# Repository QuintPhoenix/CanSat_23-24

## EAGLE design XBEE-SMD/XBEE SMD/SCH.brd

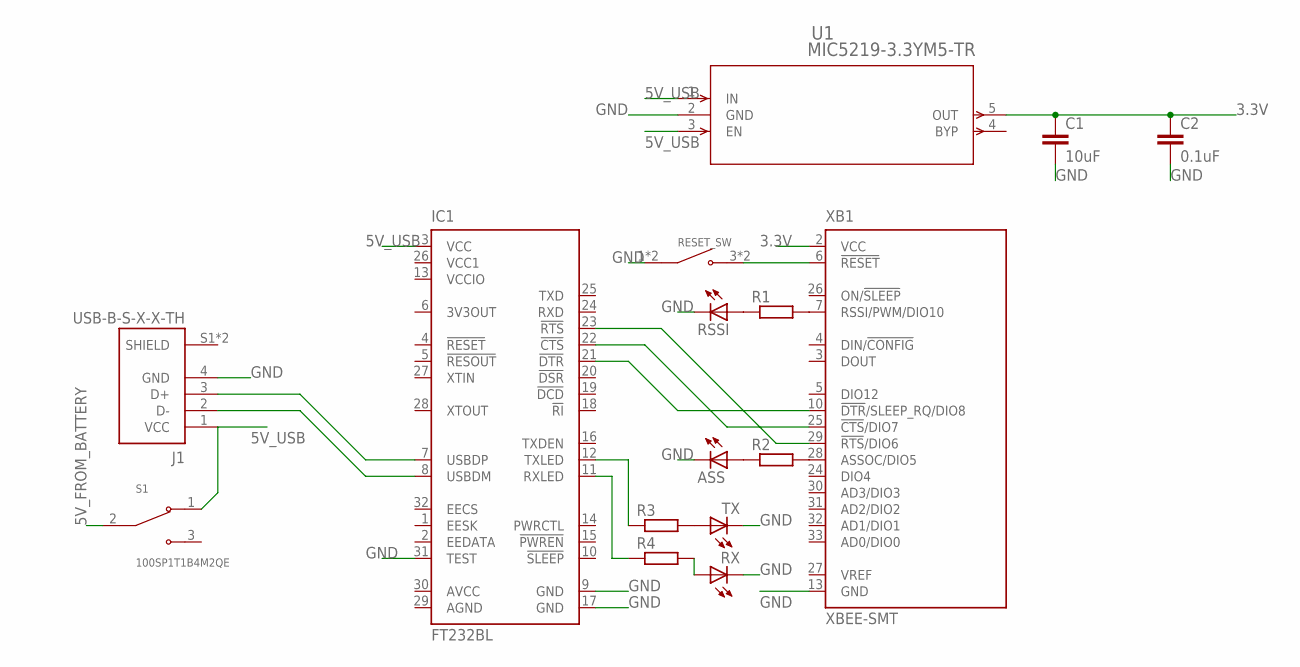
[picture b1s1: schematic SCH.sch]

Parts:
ASS: LED_E; LED_1206
C1: 10uF; C0805
C2: 0.1uF; C0805
IC1: FT232BL; LQFP32-7X7
J1: USB-B-S-X-X-TH; SAMTEC_USB-B-S-X-X-TH
R1, R2, R3, R4: R; R0805
RESET_SW: 5-1437565-0; SW_5-1437565-0
RSSI: LED_E; LED_1206
RX: LED_E; LED_1206
S1: 100SP1T1B4M2QE; SW_100SP1T1B4M2QE
TX: LED_E; LED_1206
U1: MIC5219-3.3YM5-TR; SOT-23-5_M5_MCH
XB1: XBEE-SMT

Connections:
3.3V: C1.1, C2.1, U1.5 (OUT), XB1.2 (VCC)
5V_FROM_BATTERY: S1.2
5V_USB: IC1.3 (VCC), J1.1 (VCC), S1.1, U1.1 (IN), U1.3 (EN)
AGND: IC1.29 (AGND)
AVCC: IC1.30 (AVCC)
GND: ASS.C, C1.2, C2.2, IC1.9 (GND), IC1.17 (GND), IC1.31 (TEST), J1.4 (GND), RESET_SW.1 (COM), RESET_SW.2 (COM), RSSI.C, RX.C, TX.C, U1.2 (GND), XB1.13 (GND)
unnamed: RESET_SW.3 (NO), RESET_SW.4 (NO), XB1.6 (!RESET)
unnamed: R1.2, XB1.7 (RSSI/PWM/DIO10)
unnamed: IC1.7 (USBDP), J1.3 (D+)
unnamed: IC1.8 (USBDM), J1.2 (D-)
unnamed: IC1.23 (!RTS), XB1.29 (!RTS!/DIO6)
unnamed: IC1.22 (!CTS), XB1.25 (!CTS!/DIO7)
unnamed: IC1.21 (!DTR), XB1.10 (!DTR!/SLEEP_RQ/DIO8)
unnamed: R1.1, RSSI.A
unnamed: R2.2, XB1.28 (ASSOC/DIO5)
unnamed: ASS.A, R2.1
unnamed: R3.2, TX.A
unnamed: R4.2, RX.A
unnamed: IC1.12 (TXLED), R3.1
unnamed: IC1.11 (RXLED), R4.1
VCC1: IC1.26 (VCC1)
VCCIO: IC1.13 (VCCIO)

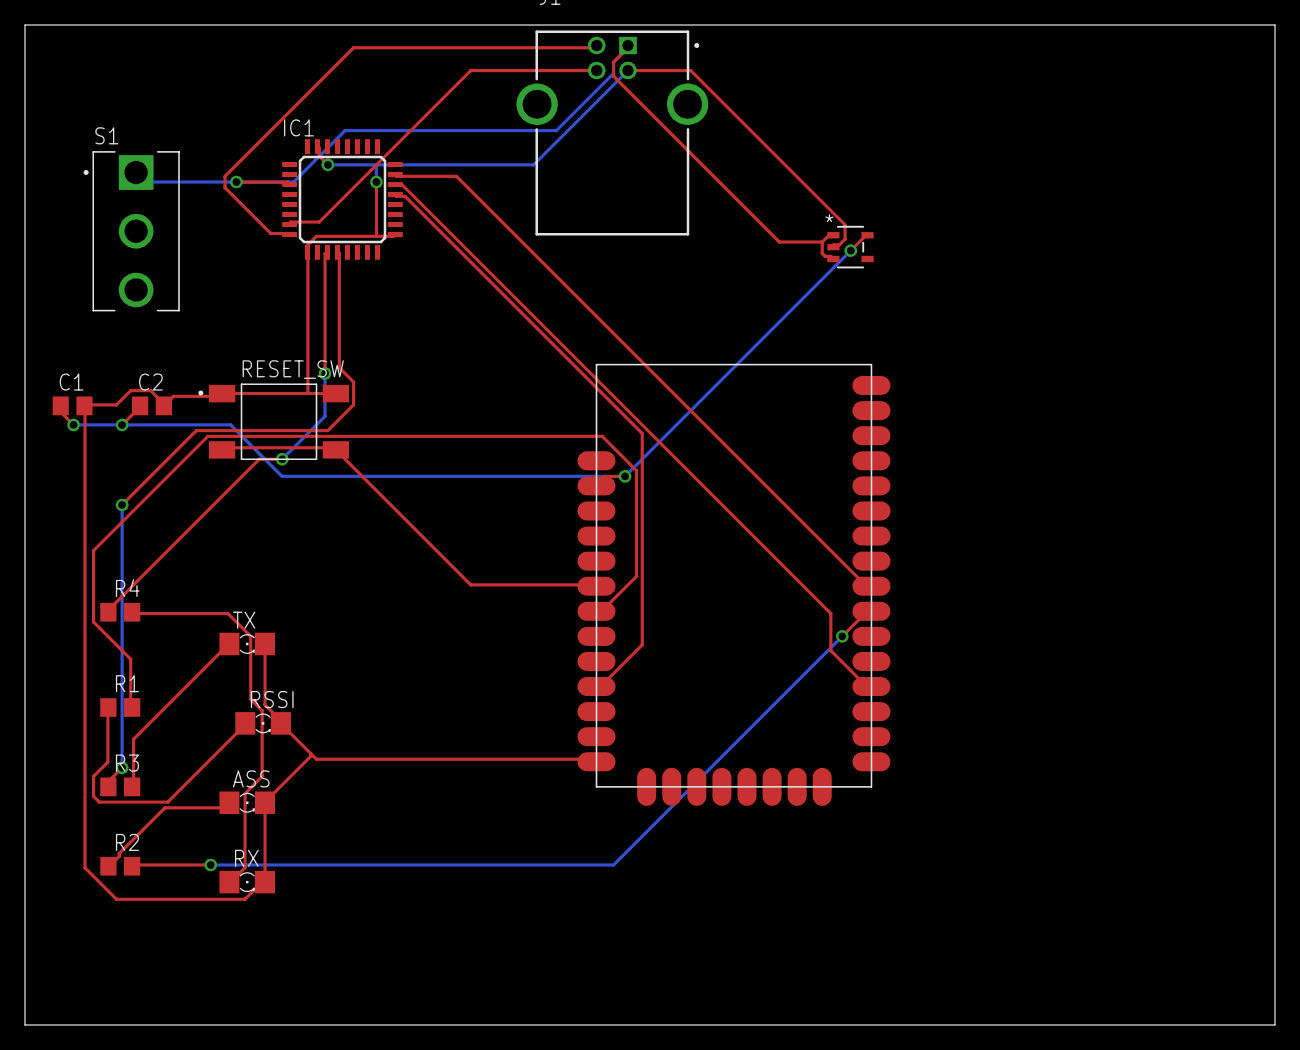
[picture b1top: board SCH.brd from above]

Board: 2 copper layers, 100.0 x 80.0 mm, 16 parts (0 on the bottom side), 17 nets.

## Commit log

2023-09-03 Intitial commit

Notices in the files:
parts and their libraries:
COPYRIGHT: Copyright (C) 2023 Ultra Librarian. All rights reserved.
